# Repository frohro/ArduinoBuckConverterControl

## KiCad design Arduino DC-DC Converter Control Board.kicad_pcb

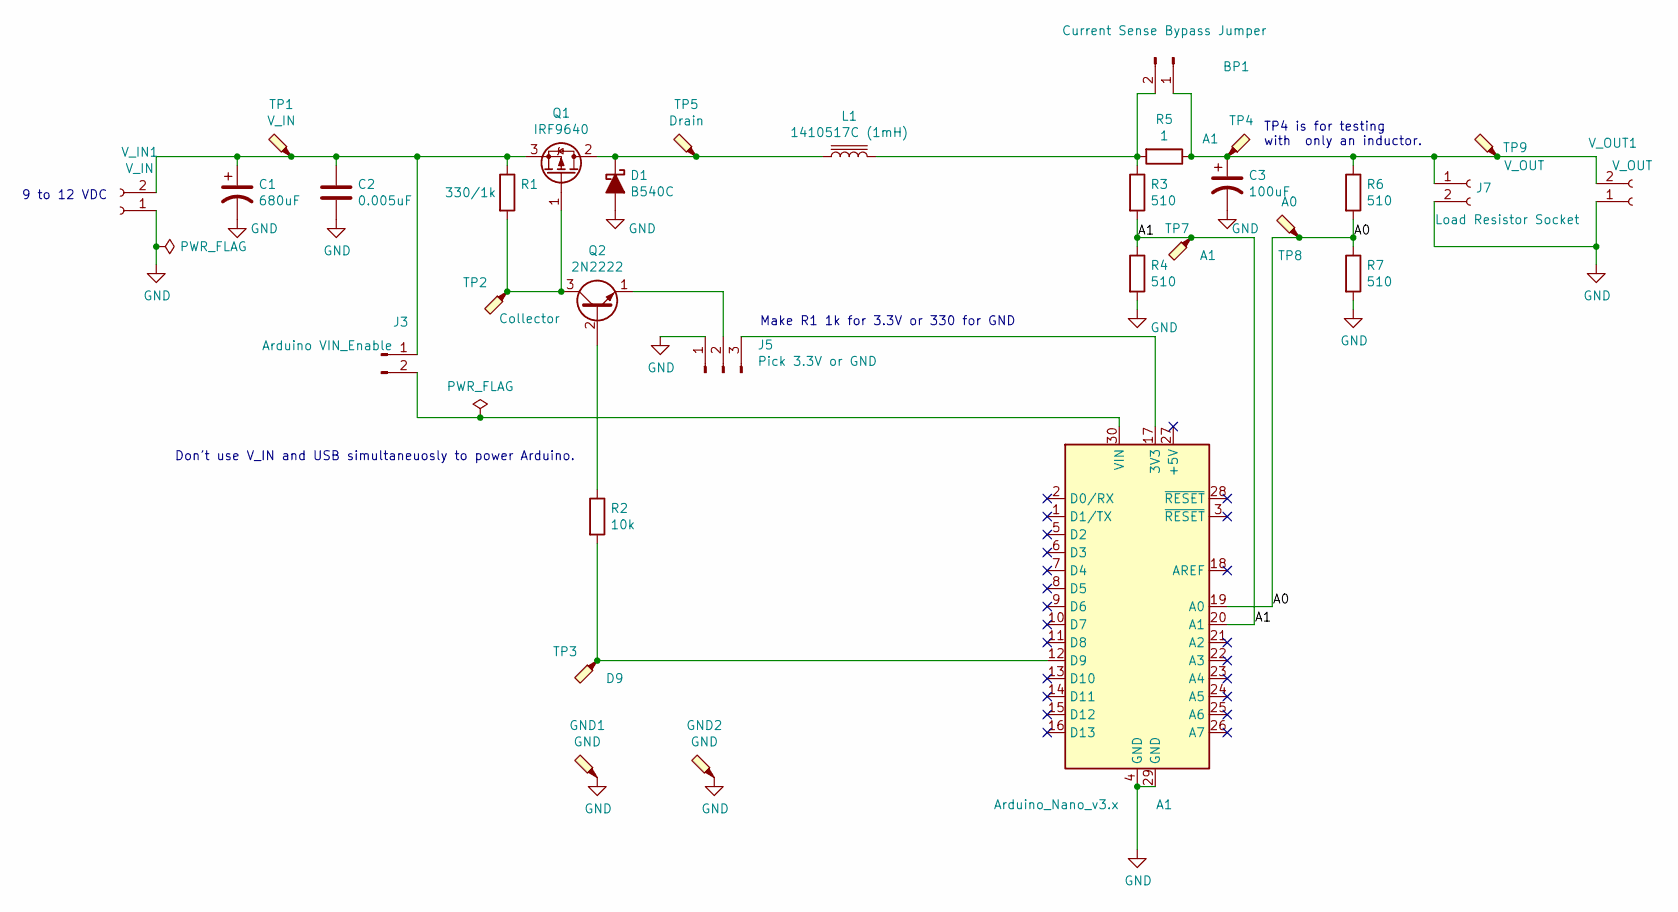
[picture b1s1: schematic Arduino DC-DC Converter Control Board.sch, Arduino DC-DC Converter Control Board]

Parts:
A1: Arduino_Nano_v3.x; Arduino_Nano
BP1: Current Sense Bypass Jumper; PinHeader_1x02_P2.54mm_Vertical
C1: 680uF; CP_Radial_D10.0mm_P7.50mm
C2: 0.005uF; C_Rect_L7.2mm_W2.5mm_P5.00mm_FKS2_FKP2_MKS2_MKP2
C3: 100uF; CP_Radial_D8.0mm_P5.00mm
D1: B540C; D_3220_8050Metric
GND1, GND2: GND; TestPoint_Keystone_5000-5004_Miniature
J3: Arduino VIN_Enable; PinHeader_1x02_P2.54mm_Vertical
J5: Pick 3.3V or GND; PinHeader_1x03_P2.54mm_Vertical
J7: Load Resistor Socket; PinSocket_1x02_P2.54mm_Vertical
L1: 1410517C (1mH); L_Radial_D29.8mm_P28.30mm_muRATA_1400series
Q1: IRF9640; TO-220F-3_Vertical
Q2: 2N2222; TO-92L_Inline
R1: 330/1k; R_Axial_DIN0207_L6.3mm_D2.5mm_P7.62mm_Horizontal
R2: 10k; R_Axial_DIN0207_L6.3mm_D2.5mm_P7.62mm_Horizontal
R3, R4, R6, R7: 510; R_Axial_DIN0207_L6.3mm_D2.5mm_P7.62mm_Horizontal
R5: 1; R_Axial_DIN0207_L6.3mm_D2.5mm_P7.62mm_Horizontal
TP1: V_IN; TestPoint_Keystone_5000-5004_Miniature
TP2: Collector; TestPoint_Keystone_5000-5004_Miniature
TP3: D9; TestPoint_Keystone_5000-5004_Miniature
TP4: A1; TestPoint_Pad_D4.0mm
TP5: Drain; TestPoint_Keystone_5000-5004_Miniature
TP7: A1; TestPoint_Keystone_5000-5004_Miniature
TP8: A0; TestPoint_Keystone_5000-5004_Miniature
TP9: V_OUT; TestPoint_Keystone_5000-5004_Miniature
V_IN1: V_IN; Banana_Jack_2Pin
V_OUT1: V_OUT; Banana_Jack_2Pin

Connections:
/A0: A1.19 (A0), R6.2, R7.1, TP8.1
/A1: A1.20 (A1), R3.2, R4.1, TP7.1
GND: A1.4 (GND), A1.29 (GND), C1.2, C2.2, C3.2, D1.2 (A), GND1.1, GND2.1, J5.1, J7.2, R4.2, R7.2, V_IN1.1, V_OUT1.1
unnamed: A1.12 (D9), R2.2, TP3.1
unnamed: A1.17 (3V3), J5.3
unnamed: A1.30 (VIN), J3.2
unnamed: BP1.1, C3.1, J7.1, R5.1, R6.1, TP4.1, TP9.1, V_OUT1.2
unnamed: BP1.2, L1.2, R3.1, R5.2
unnamed: C1.1, C2.1, J3.1, Q1.3 (S), R1.1, TP1.1, V_IN1.2
unnamed: D1.1 (K), L1.1, Q1.2 (D), TP5.1
unnamed: J5.2, Q2.1 (E)
unnamed: Q1.1 (G), Q2.3 (C), R1.2, TP2.1
unnamed: Q2.2 (B), R2.1

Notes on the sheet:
9 to 12 VDC
Don't use V_IN and USB simultaneuosly to power Arduino.
Make R1 1k for 3.3V or 330 for GND
TP4 is for testing with only an inductor.

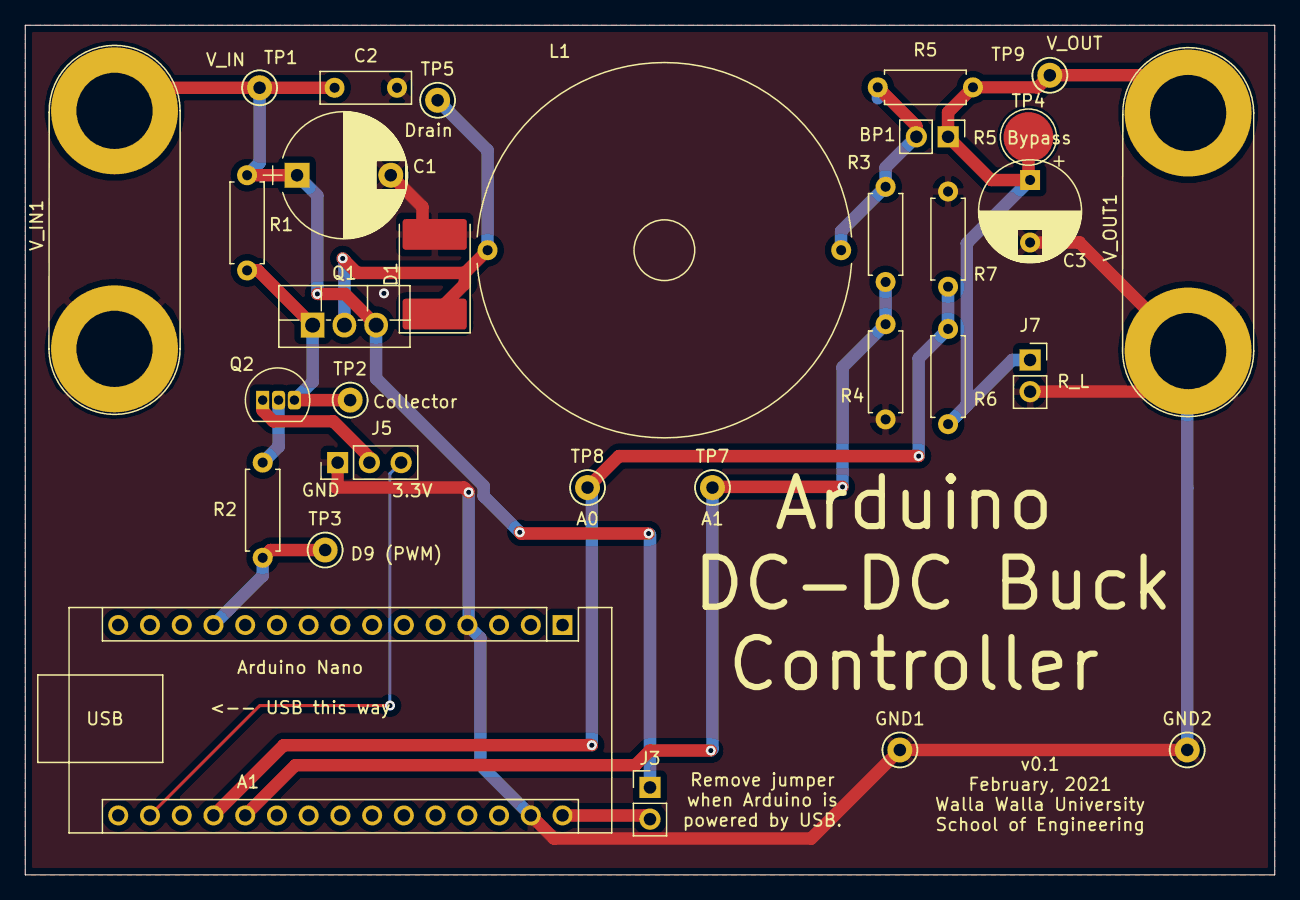
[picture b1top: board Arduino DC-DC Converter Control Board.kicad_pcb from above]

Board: 2 copper layers, 100.0 x 68.0 mm, 31 parts (0 on the bottom side), 13 nets.

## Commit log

2021-04-28 Added LTspice files.
